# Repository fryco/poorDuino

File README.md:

# poorDuino
Arduino-like simple development board

## Idea
Main purpose of designing `poorDuino` was to *utilize* dozen Atmega8/Atmega168 chips, which were collected by me, for last few years. I do like Arduino as a form factor and don't like as IDE. Thus I decided to design this board to fulfil my not so sophisticated expectations: keep compatibility with original Arduino Uno and no support for programming via USB (ISP FTW!).

`poorDuino`'s name comes from reduced manufacturing costs (i.e. no USB programmer onboard). It might be decreased more, but it would not fulfill my needs.

##Features
* Arduino UNO board shape,
* Connectors are fully compatible with Arduino standard,
* Two power supply: 5V and 3V3 (selected via jumper),
* Extra pull-up resitors on IIC lines (enabled by soldering jumper on bottom of the board),
* USB connector and USB2UART bridge removed,
* ICSP connector for programming (external programmer is necessary)

## Resources
1. Arduino UNO https://www.arduino.cc/en/Main/arduinoBoardUno

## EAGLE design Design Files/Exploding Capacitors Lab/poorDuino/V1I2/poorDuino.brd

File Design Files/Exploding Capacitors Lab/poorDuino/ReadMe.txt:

Examples of other directory names:
V1I1A - only BOM changes
V1I2 - pin compatible with V1I1, no big changes
V2I1 - not compatible with V1

This is also place for backups. Pack V1I1 Directory, add date and possibly a note:
V1I1 2011 01 10
V1I1 2011 02 21 Schematic Checked

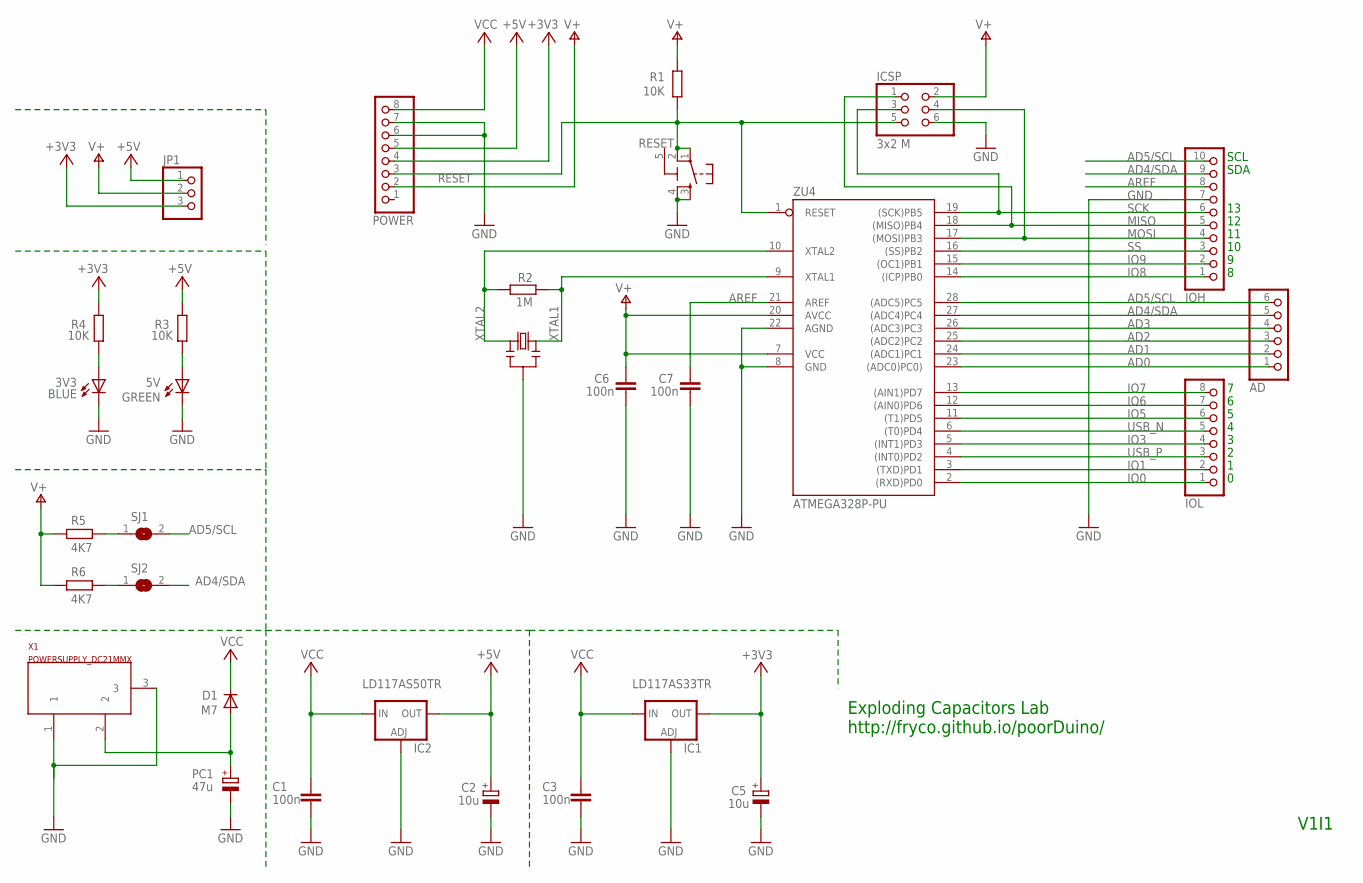
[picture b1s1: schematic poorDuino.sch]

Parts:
3V3: BLUE; CHIP-LED0805
5V: GREEN; CHIP-LED0805
AD: 6x1F-H8.5; 1X06
C1, C3, C6, C7: 100n; C0805
C2, C5: 10u; SMC_A
D1: M7; SMB
IC1: LD117AS33TR; SOT223
IC2: LD117AS50TR; SOT223
ICSP: 3x2 M; 2X03
IOH: 10x1F-H8.5; 1X10
IOL: 8x1F-H8.5; 1X08
JP1: PINHD-1X3; 1X03
PC1: 47u; PANASONIC_D
POWER: 8x1F-H8.5; 1X08
R1, R3, R4: 10K; R0805
R2: 1M; R0805
R5, R6: 4K7; R0805
RESET: TS42031-160R-TR-7260; TS42
SJ1, SJ2: SJ
X1: POWERSUPPLY_DC21MMX; POWERSUPPLY_DC-21MM
Y2: CSTCE16M0V53-R0 16MHZ; RESONATOR
ZU4: ATMEGA328P-PU; DIL28-3

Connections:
5-GND: RESET.5 (5-GND)
+3V3: C5.+, IC1.4 (OUT), JP1.3, POWER.4, R4.1
+5V: C2.+, IC2.4 (OUT), JP1.1, POWER.5, R3.1
AD0: AD.1, ZU4.23 ((ADC0)PC0))
AD1: AD.2, ZU4.24 ((ADC1)PC1)
AD2: AD.3, ZU4.25 ((ADC2)PC2)
AD3: AD.4, ZU4.26 ((ADC3)PC3)
AD4/SDA: AD.5, IOH.9, SJ2.2, ZU4.27 ((ADC4)PC4)
AD5/SCL: AD.6, IOH.10, SJ1.2, ZU4.28 ((ADC5)PC5)
AREF: C7.2, IOH.8, ZU4.21 (AREF)
GND: 3V3.C, 5V.C, C1.1, C2.-, C3.1, C5.-, C6.1, C7.1, IC1.1 (ADJ), IC2.1 (ADJ), ICSP.6, IOH.7, PC1.-, POWER.6, POWER.7, RESET.3, RESET.4, X1.1, X1.3, Y2.2, ZU4.8 (GND), ZU4.22 (AGND)
IO0: IOL.1, ZU4.2 ((RXD)PD0)
IO1: IOL.2, ZU4.3 ((TXD)PD1)
IO3: IOL.4, ZU4.5 ((INT1)PD3)
IO5: IOL.6, ZU4.11 ((T1)PD5)
IO6: IOL.7, ZU4.12 ((AIN0)PD6)
IO7: IOL.8, ZU4.13 ((AIN1)PD7)
IO8: IOH.1, ZU4.14 ((ICP)PB0)
IO9: IOH.2, ZU4.15 ((OC1)PB1)
MISO: ICSP.1, IOH.5, ZU4.18 ((MISO)PB4)
MOSI: ICSP.4, IOH.4, ZU4.17 ((MOSI)PB3)
unnamed: 3V3.A, R4.2
unnamed: 5V.A, R3.2
unnamed: R5.1, SJ1.1
unnamed: R6.1, SJ2.1
PWRIN: D1.A, PC1.+, X1.2
RESET: ICSP.5, POWER.3, R1.1, RESET.1, RESET.2, ZU4.1 (RESET)
SCK: ICSP.3, IOH.6, ZU4.19 ((SCK)PB5)
SS: IOH.3, ZU4.16 ((SS)PB2)
USB_N: IOL.5, ZU4.6 ((T0)PD4)
USB_P: IOL.3, ZU4.4 ((INT0)PD2)
V+: C6.2, ICSP.2, JP1.2, POWER.2, R1.2, R5.2, R6.2, ZU4.7 (VCC), ZU4.20 (AVCC)
VCC: C1.2, C3.2, D1.C, IC1.3 (IN), IC2.3 (IN), POWER.8
XTAL1: R2.1, Y2.3, ZU4.9 (XTAL1)
XTAL2: R2.2, Y2.1, ZU4.10 (XTAL2)

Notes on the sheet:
Exploding Capacitors Lab http://fryco.github.io/poorDuino/
SDA
SCL
V1I1

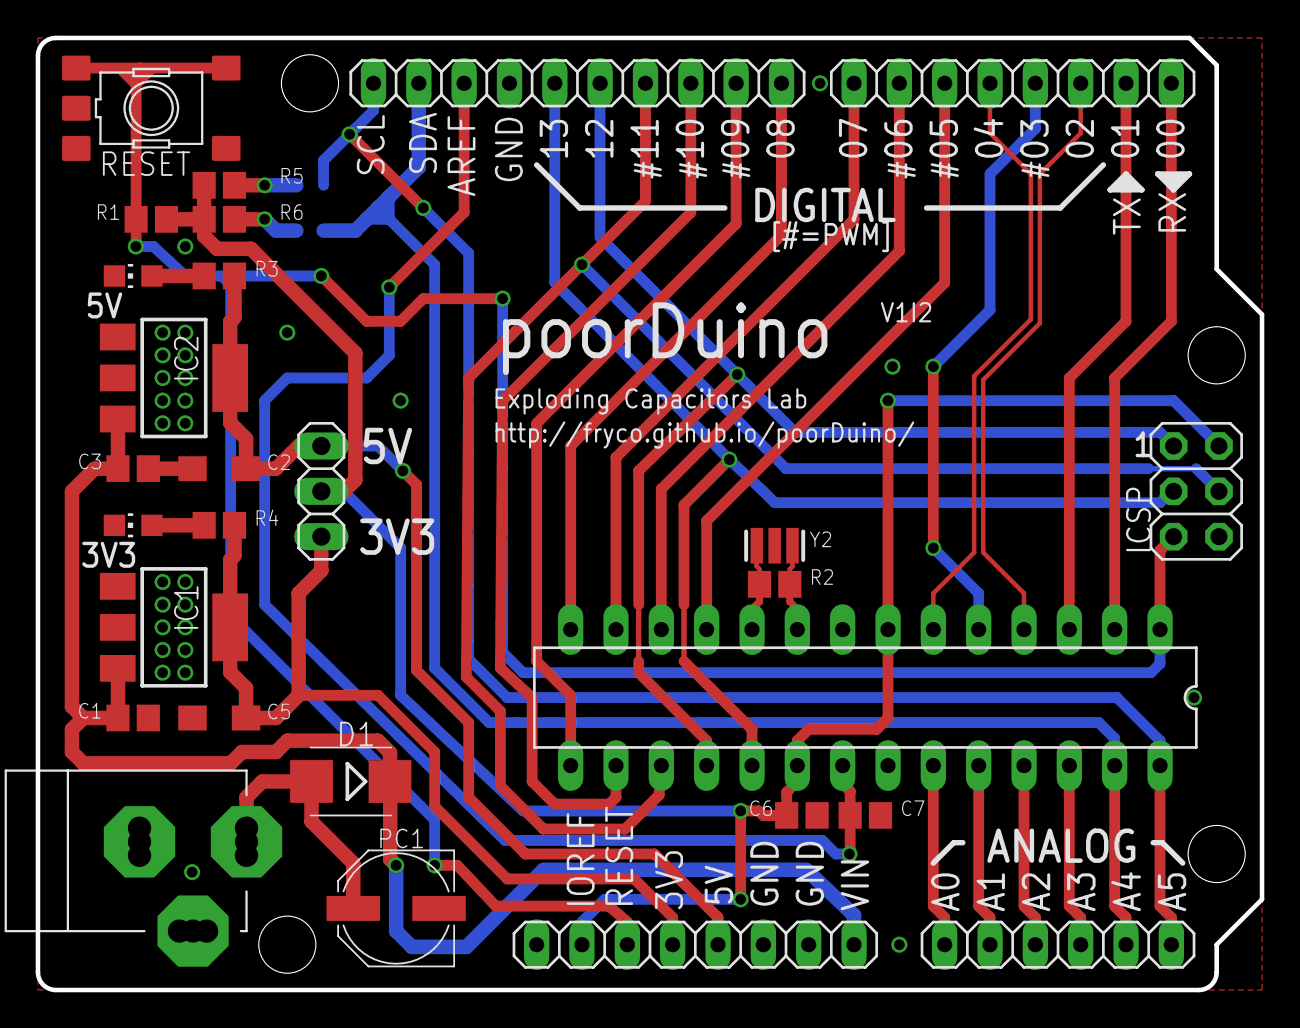
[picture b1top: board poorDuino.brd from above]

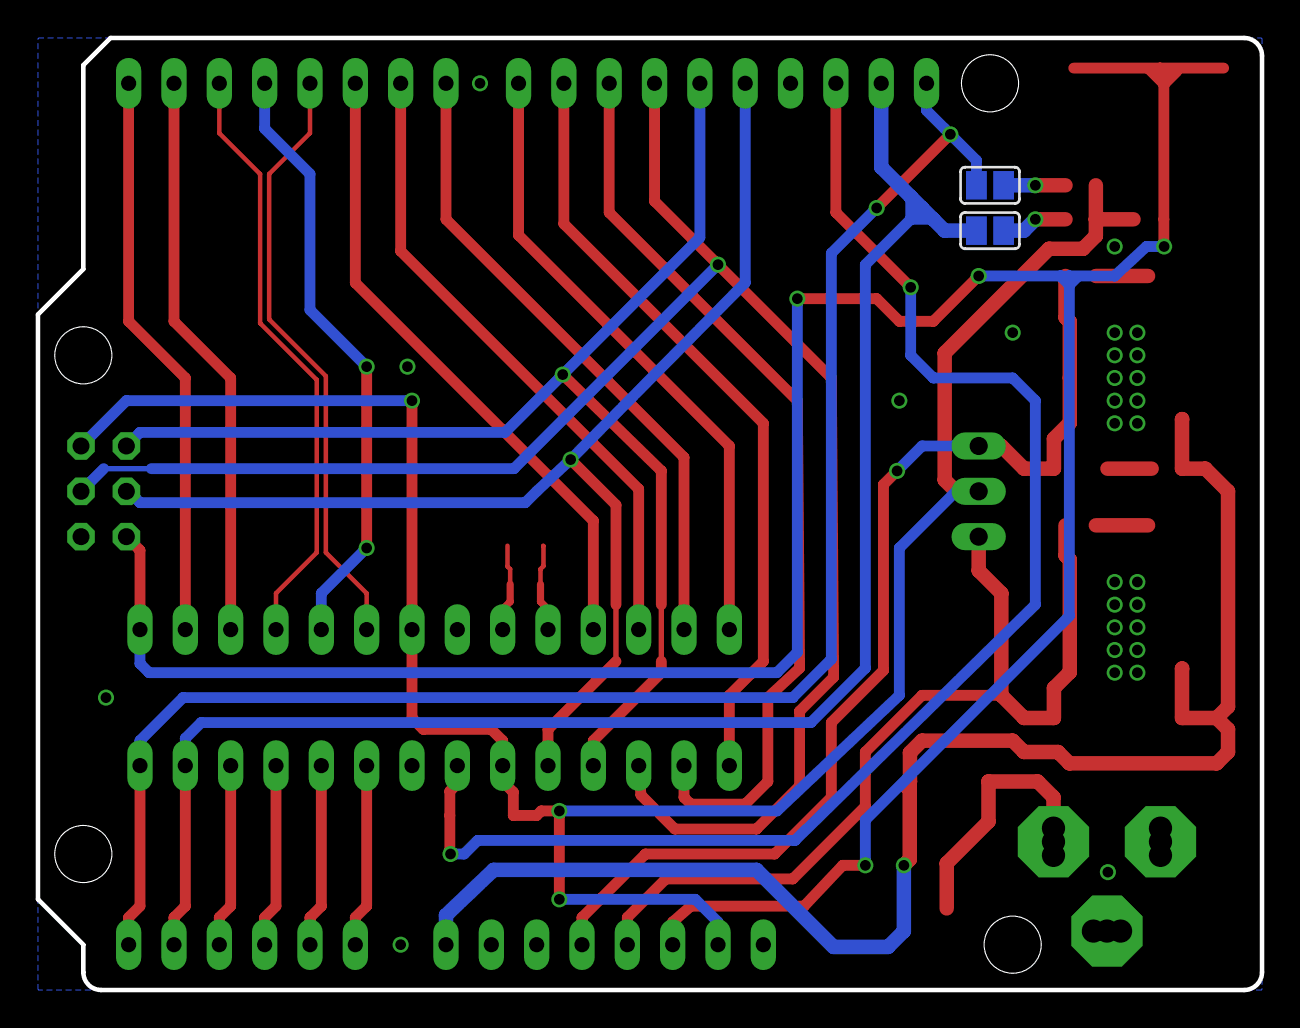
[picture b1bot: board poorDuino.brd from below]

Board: 2 copper layers, 68.6 x 53.3 mm, 30 parts (2 on the bottom side), 34 nets.

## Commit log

2015-08-19 Directory tree update
2015-08-19 Atmega16U2 with surroundings removed
2015-08-19 .gitignore update
2015-08-19 Create gh-pages branch via GitHub
2015-08-19 Power supply modification
    LDOs, which were originaly in Arduino project, have been replaced to
    LD1117xxx. /schematic only/
2015-08-19 Schematic cleanup
    3V3 LED status added
2015-08-19 First attempt to PCB design
2015-08-20 ReadMe.txt removed
2015-08-20 PCB layout
2015-08-20 PCB layout update
2015-08-21 README.md update
2015-08-21 DirtyPCB Eagle specyfic files added
2015-08-21 PCB update
2015-08-21 SCH update
2015-08-21 V1I1 is ready!
2015-08-21 V1I1 is ready
2015-08-21 BackMeUp.py script modification
    ZIP file name is modified. Now it looks like:
    project_name+version+date+timestamp.zip
2015-08-21 V1I1 backup added
2015-08-21 Release files update
2015-08-21 BackeMeUp.py update
2015-08-27 PCB layout improvement
    - Better grounding
    - Re-alignment of few elements/routes
    - Removed useless labels from the bottom of the board
    - RCL labels alignment
2015-08-27 Backup update
2015-08-31 V1I2 branched out
2015-08-31 Differential pair routing applied to traces related to V-USB support (DIO2 and DIO4)
2015-08-31 Dir structure update
2015-08-31 V1I1 design files were missing. Added them back to repo.
2015-08-31 PCB layout V1I2 is ready
2015-08-31 V1I2 release files update.
